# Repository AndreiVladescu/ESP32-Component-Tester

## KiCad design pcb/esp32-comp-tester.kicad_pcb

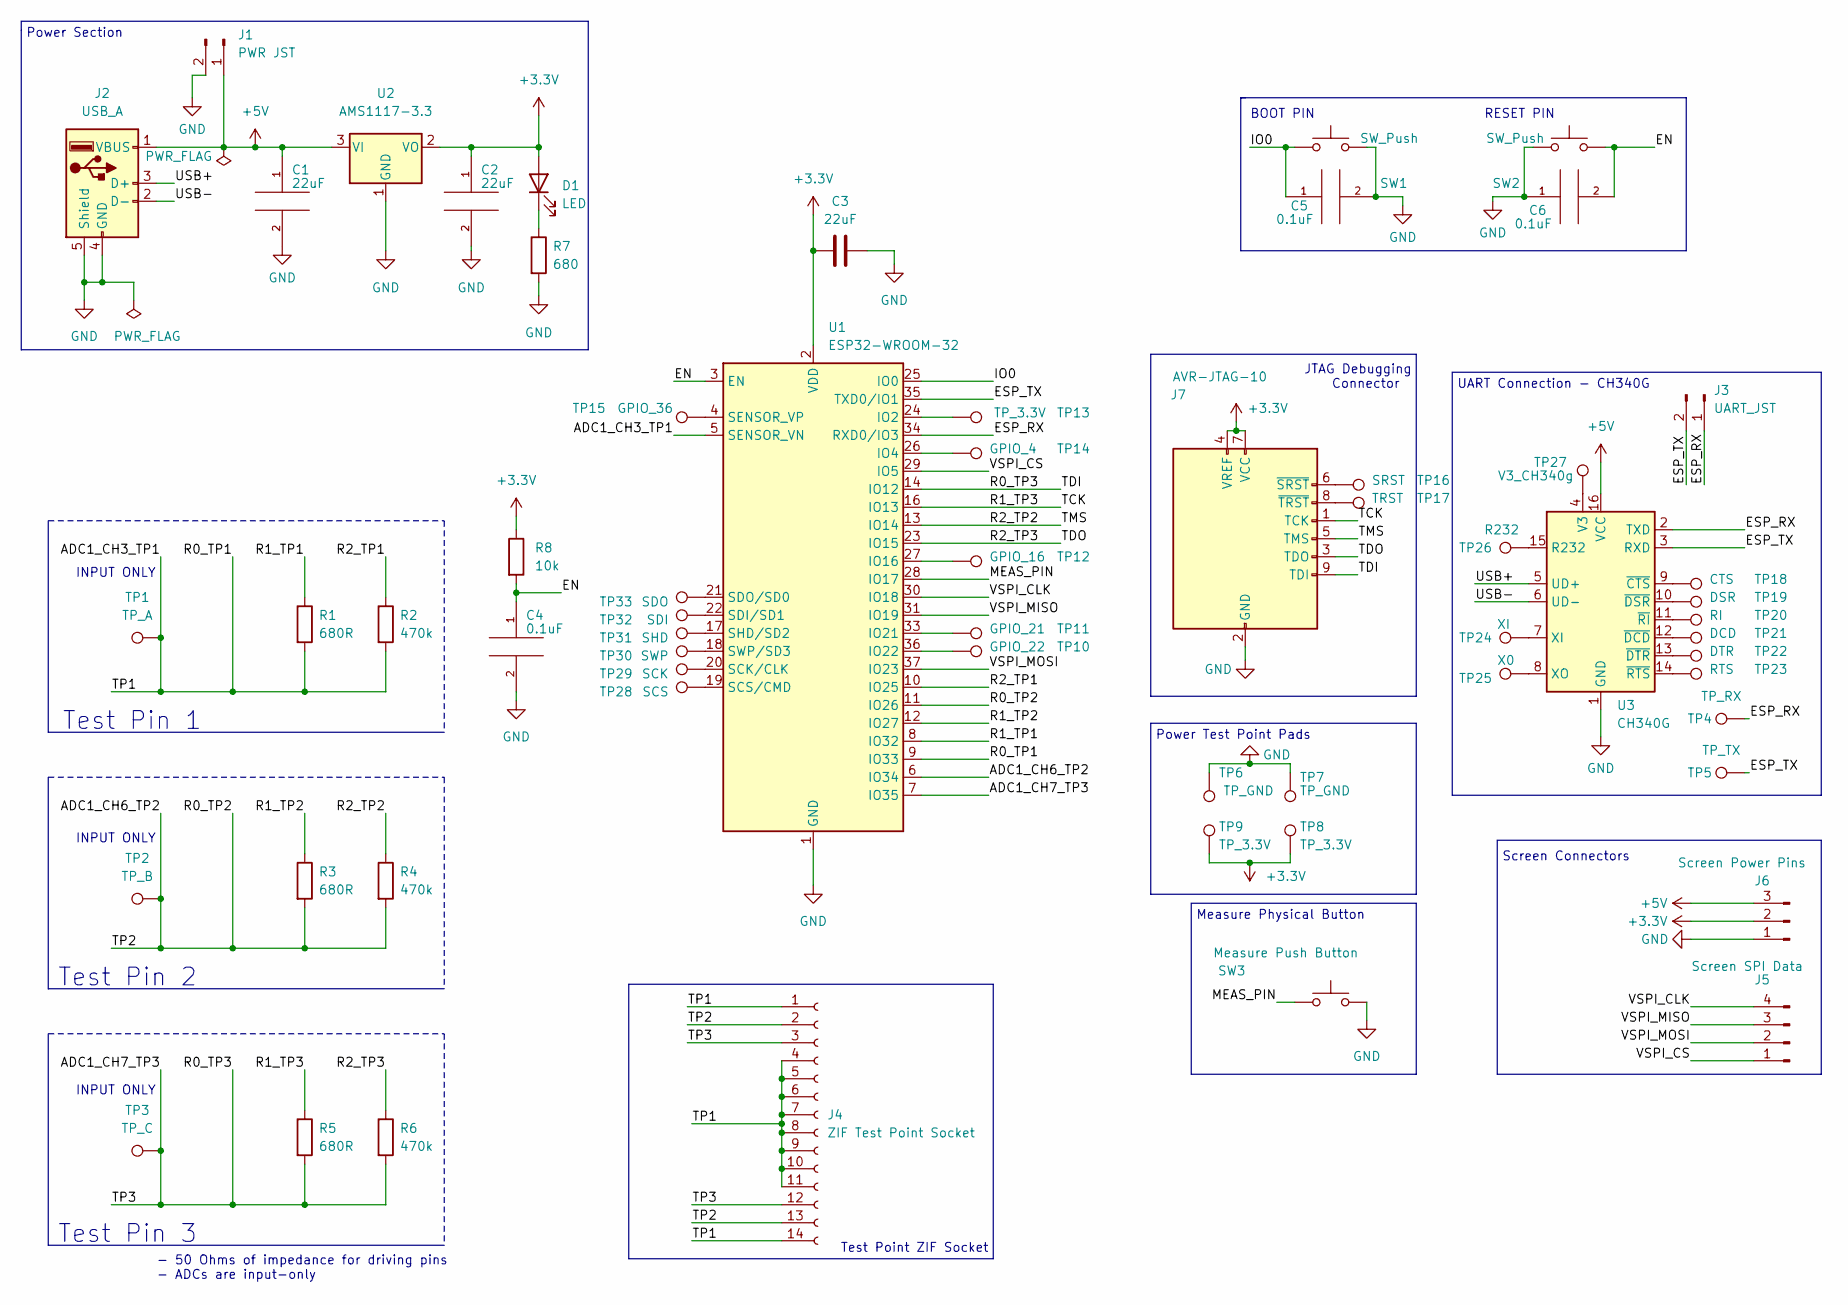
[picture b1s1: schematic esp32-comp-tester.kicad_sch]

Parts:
C1, C2, C3: 22uF; C_1206_3216Metric
C4, C5, C6: 0.1uF; C_0603_1608Metric
D1: LED; LED_1206_3216Metric
J1: PWR JST; PinSocket_1x02_P2.54mm_Vertical
J2: USB_A; USB_A_Molex_48037-2200_Horizontal
J3: UART_JST; PinSocket_1x02_P2.54mm_Vertical
J4: ZIF Test Point Socket; DIP-14_W7.62mm_Socket
J5: Screen SPI Data; JST_EH_B4B-EH-A_1x04_P2.50mm_Vertical
J6: Screen Power Pins; JST_EH_B3B-EH-A_1x03_P2.50mm_Vertical
J7: AVR-JTAG-10; IDC-Header_2x05_P2.54mm_Vertical
R1, R3, R5: 680R; R_1206_3216Metric
R2, R4, R6: 470k; R_1206_3216Metric
R7: 680; R_1206_3216Metric
R8: 10k; R_1206_3216Metric
SW1, SW2: SW_Push; SW_SPST_B3S-1000
SW3: Measure Push Button; SW_SPST_B3S-1100
TP1: TP_A; TestPoint_Pad_D2.0mm
TP2: TP_B; TestPoint_Pad_D2.0mm
TP3: TP_C; TestPoint_Pad_D2.0mm
TP4: TP_RX; TestPoint_Pad_D2.0mm
TP5: TP_TX; TestPoint_Pad_D2.0mm
TP6, TP7: TP_GND; TestPoint_Pad_D2.0mm
TP8, TP9, TP13: TP_3.3V; TestPoint_Pad_D2.0mm
TP10: GPIO_22; TestPoint_Pad_D2.0mm
TP11: GPIO_21; TestPoint_Pad_D2.0mm
TP12: GPIO_16; TestPoint_Pad_D2.0mm
TP14: GPIO_4; TestPoint_Pad_D2.0mm
TP15: GPIO_36; TestPoint_Pad_D2.0mm
TP16: SRST; TestPoint_Pad_D2.0mm
TP17: TRST; TestPoint_Pad_D2.0mm
TP18: CTS; TestPoint_Pad_D2.0mm
TP19: DSR; TestPoint_Pad_D2.0mm
TP20: RI; TestPoint_Pad_D2.0mm
TP21: DCD; TestPoint_Pad_D2.0mm
TP22: DTR; TestPoint_Pad_D2.0mm
TP23: RTS; TestPoint_Pad_D2.0mm
TP24: XI; TestPoint_Pad_D2.0mm
TP25: X0; TestPoint_Pad_D2.0mm
TP26: R232; TestPoint_Pad_D2.0mm
TP27: V3_CH340g; TestPoint_Pad_D2.0mm
TP28: SCS; TestPoint_Pad_D2.0mm
TP29: SCK; TestPoint_Pad_D2.0mm
TP30: SWP; TestPoint_Pad_D2.0mm
TP31: SHD; TestPoint_Pad_D2.0mm
TP32: SDI; TestPoint_Pad_D2.0mm
TP33: SDO; TestPoint_Pad_D2.0mm
U1: ESP32-WROOM-32
U2: AMS1117-3.3; SOT-223-3_TabPin2
U3: CH340G; SOIC-16_3.9x9.9mm_P1.27mm

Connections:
+3.3V: C2.1, C3.1, D1.2 (A), J6.2, J7.4 (VREF), J7.7 (VCC), R8.1, TP8.1, TP9.1, U1.2 (VDD), U2.2 (VO)
+5V: C1.1, J1.1, J2.1 (VBUS), J6.3, U2.3 (VI), U3.16 (VCC)
/ADC1_CH3_TP1: J4.1, J4.4, J4.5, J4.6, J4.7, J4.8, J4.9, J4.10, J4.11, J4.14, R1.2, R2.2, TP1.1, U1.5 (SENSOR_VN), U1.9 (IO33)
/ADC1_CH6_TP2: J4.2, J4.13, R3.2, R4.2, TP2.1, U1.6 (IO34), U1.11 (IO26)
/ADC1_CH7_TP3: J4.3, J4.12, J7.9 (TDI), R5.2, R6.2, TP3.1, U1.7 (IO35), U1.14 (IO12)
/EN: C4.1, C6.2, R8.2, SW2.2, U1.3 (EN)
/ESP_RX: J3.1, TP4.1, U1.34 (RXD0/IO3), U3.2 (TXD)
/ESP_TX: J3.2, TP5.1, U1.35 (TXD0/IO1), U3.3 (RXD)
/IO0: C5.1, SW1.1, U1.25 (IO0)
/MEAS_PIN: SW3.1, U1.28 (IO17)
/R1_TP1: R1.1, U1.8 (IO32)
/R1_TP2: R3.1, U1.12 (IO27)
/R1_TP3: J7.1 (TCK), R5.1, U1.16 (IO13)
/R2_TP1: R2.1, U1.10 (IO25)
/R2_TP2: J7.5 (TMS), R4.1, U1.13 (IO14)
/R2_TP3: J7.3 (TDO), R6.1, U1.23 (IO15)
/USB+: J2.3 (D+), U3.5 (UD+)
/USB-: J2.2 (D-), U3.6 (UD-)
/VSPI_CLK: J5.4, U1.30 (IO18)
/VSPI_CS: J5.1, U1.29 (IO5)
/VSPI_MISO: J5.3, U1.31 (IO19)
/VSPI_MOSI: J5.2, U1.37 (IO23)
GND: C1.2, C2.2, C3.2, C4.2, C5.2, C6.1, J1.2, J2.4 (GND), J2.5 (Shield), J6.1, J7.2 (GND), J7.10 (GND), R7.2, SW1.2, SW2.1, SW3.2, TP6.1, TP7.1, U1.1 (GND), U1.15 (GND), U1.38 (GND), U1.39 (GND), U2.1 (GND), U3.1 (GND)
unnamed: D1.1 (K), R7.1
unnamed: J7.6 (~SRST), TP16.1
unnamed: J7.8 (~TRST), TP17.1
unnamed: TP13.1, U1.24 (IO2)
unnamed: TP14.1, U1.26 (IO4)
unnamed: TP12.1, U1.27 (IO16)
unnamed: TP11.1, U1.33 (IO21)
unnamed: TP10.1, U1.36 (IO22)
unnamed: TP29.1, U1.20 (SCK/CLK)
unnamed: TP28.1, U1.19 (SCS/CMD)
unnamed: TP32.1, U1.22 (SDI/SD1)
unnamed: TP33.1, U1.21 (SDO/SD0)
unnamed: TP15.1, U1.4 (SENSOR_VP)
unnamed: TP31.1, U1.17 (SHD/SD2)
unnamed: TP30.1, U1.18 (SWP/SD3)
unnamed: TP26.1, U3.15 (R232)
unnamed: TP27.1, U3.4 (V3)
unnamed: TP24.1, U3.7 (XI)
unnamed: TP25.1, U3.8 (XO)
unnamed: TP18.1, U3.9 (~CTS)
unnamed: TP21.1, U3.12 (~DCD)
unnamed: TP19.1, U3.10 (~DSR)
unnamed: TP22.1, U3.13 (~DTR)
unnamed: TP20.1, U3.11 (~RI)
unnamed: TP23.1, U3.14 (~RTS)

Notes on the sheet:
INPUT ONLY
Screen Connectors
JTAG Debugging Connector
- 50 Ohms of impedance for driving pins - ADCs are input-only
Power Test Point Pads
Test Pin 1
BOOT PIN
Test Pin 3
Measure Physical Button
Power Section
UART Connection - CH340G
RESET PIN
Test Point ZIF Socket
Test Pin 2

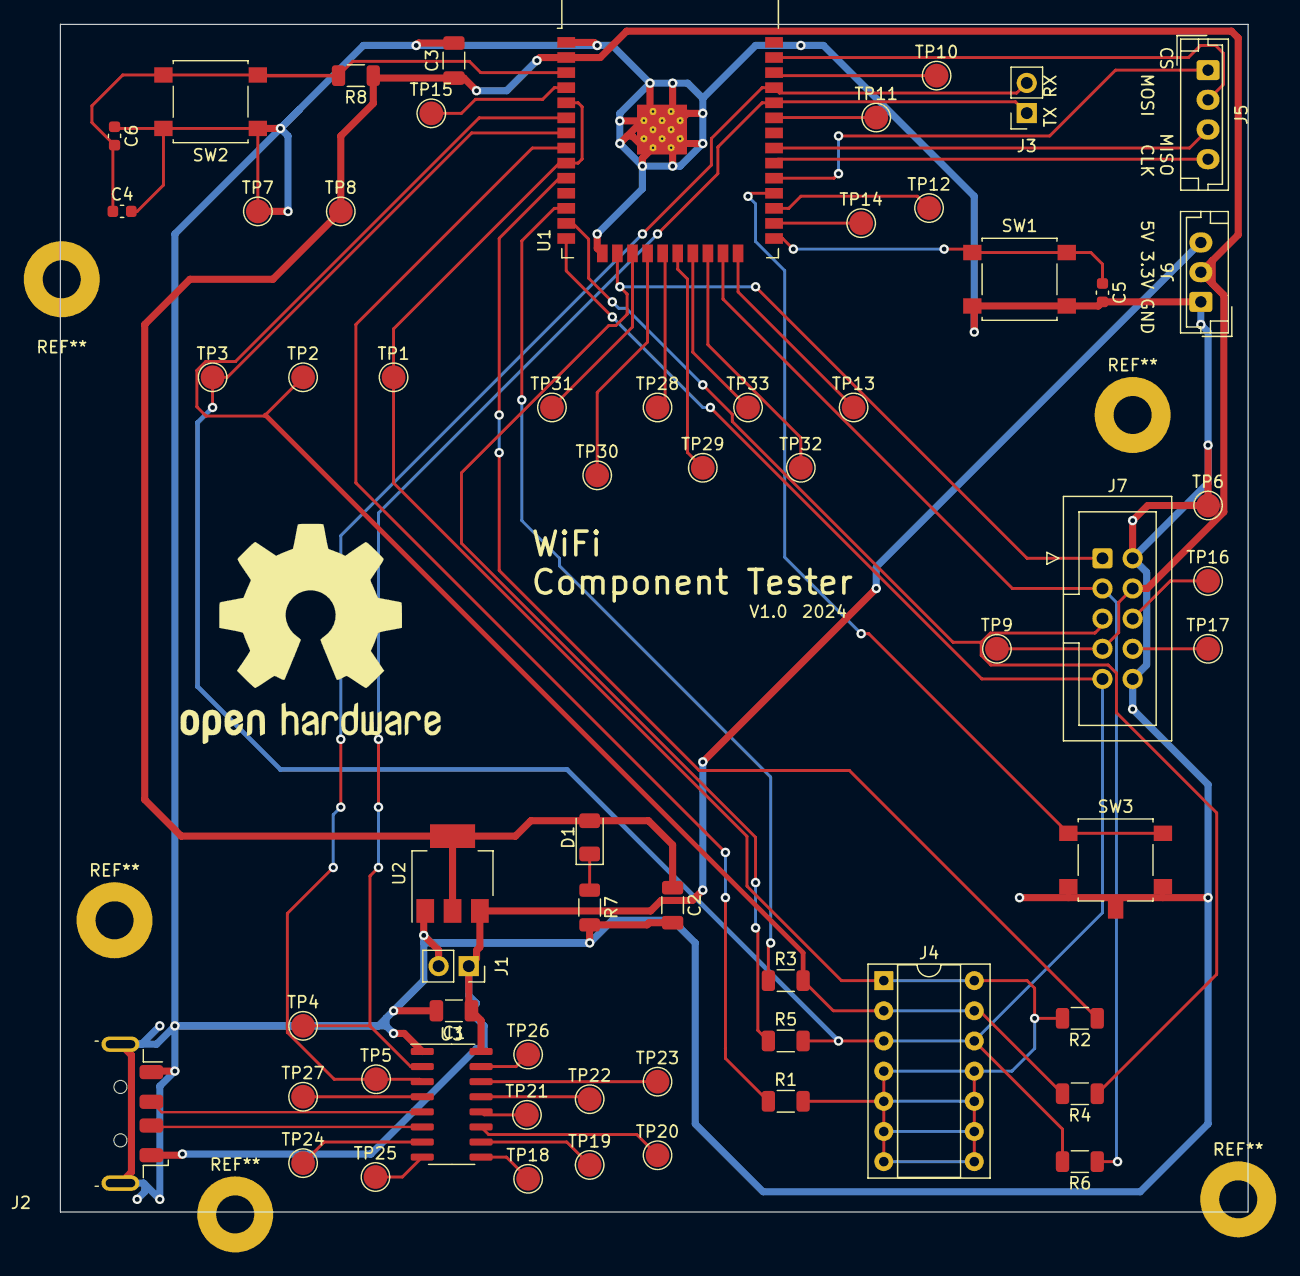
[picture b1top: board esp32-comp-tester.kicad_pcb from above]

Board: 2 copper layers, 100.0 x 100.0 mm, 61 parts (0 on the bottom side), 48 nets.

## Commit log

2024-04-15 Add files via upload
    Persistent User Prompt
2024-04-29 Added resistance measurement stubs
2024-04-29 Improved debug prints
2024-04-30 Split main into conf
2024-04-30 Added dummy threaded web server
2024-04-30 Added template
2024-04-30 Fixed dynamic template + css
2024-04-30 Made the web server wait longer
2024-04-30 Resistance sanity check
2024-05-10 Added schematic
2024-05-13 Update measure_resistance()
2024-05-13 Added no wifi mode
2024-05-13 Added dummy host app
2024-05-13 Added mDNS and WiFi credentials storing
2024-05-13 Added serial comms
2024-05-13 Added "sys" missing import
2024-05-13 Added capacitance measuring stubs
2024-05-13 Fixed indents
2024-05-13 Added KiCAD Project
2024-05-14 Updated Schematic
2024-05-14 New pdf schematic
2024-05-14 Updated gitignore
2024-05-15 Fixed resistance measuring
2024-05-15 Removed irrelevant comments
2024-05-16 Code refactoring
2024-05-16 Added capacitance measuring
2024-05-16 Fixed 470k resistance measuring
2024-05-17 Added V1 PCB
2024-05-17 Little PCB Changes
2024-05-17 Resistance Measurement Averaging
2024-05-18 Added diode measuring
2024-05-18 Ignore hardcoded wifi_credentials
2024-05-18 Fixed capacitor testing
2024-05-20 Added case
2024-05-20 Added multiple case formats
2024-05-20 Added dc barrel jack
2024-05-20 Added measuring button
2024-05-20 Modified the html style
2024-05-20 Diode capacitor fix
2024-05-21 Updated website rendering
2024-05-21 Added html for all components
2024-05-23 Added inductor measurement
2024-06-08 bug-fixes
2024-08-01 Added quality and dissipation factors
2024-08-11 Added Q & D factors for inductors
